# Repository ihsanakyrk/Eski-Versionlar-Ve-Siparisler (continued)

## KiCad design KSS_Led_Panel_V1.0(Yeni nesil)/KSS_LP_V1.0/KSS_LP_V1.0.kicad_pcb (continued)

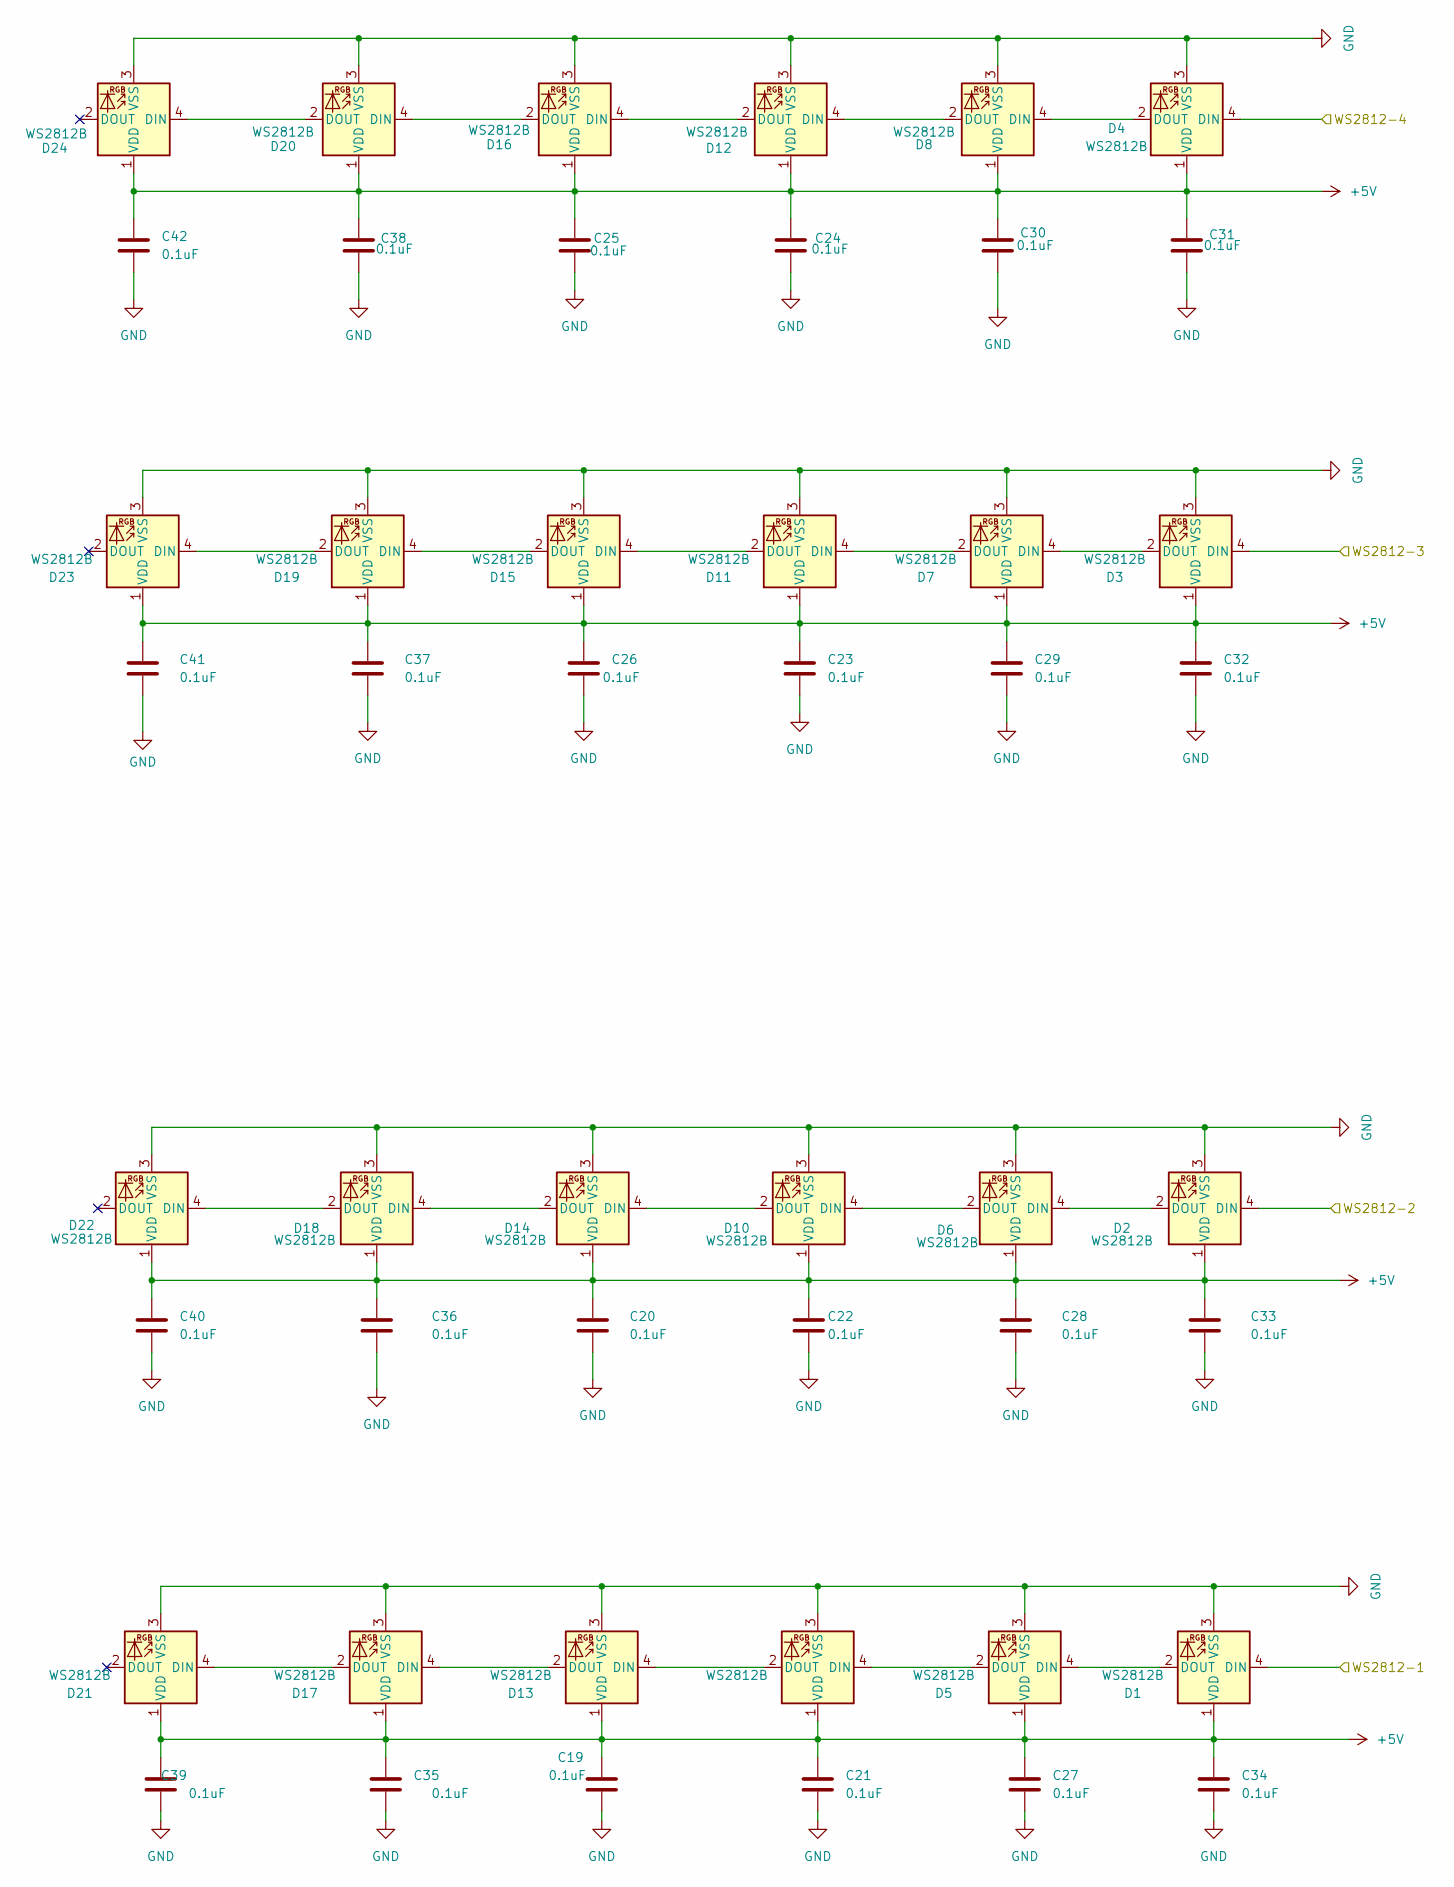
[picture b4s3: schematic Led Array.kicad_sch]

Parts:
C19, C20, C21, C22, C23, C24, C25, C26, C27, C28, C29, C30, C31, C32, C33, C34, C35, C36, C37, C38, C39, C40, C41, C42: 0.1uF; C_0603_1608Metric
D1, D2, D3, D4, D5, D6, D7, D8, D9, D10, D11, D12, D13, D14, D15, D16, D17, D18, D19, D20, D21, D22, D23, D24: WS2812B; LED_WS2812B_PLCC4_5.0x5.0mm_P3.2mm

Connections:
+5V: C19.1, C20.1, C21.1, C22.1, C23.1, C24.1, C25.1, C26.1, C27.1, C28.1, C29.1, C30.1, C31.1, C32.1, C33.1, C34.1, C35.1, C36.1, C37.1, C38.1, C39.1, C40.1, C41.1, C42.1, D1.1 (VDD), D2.1 (VDD), D3.1 (VDD), D4.1 (VDD), D5.1 (VDD), D6.1 (VDD), D7.1 (VDD), D8.1 (VDD), D9.1 (VDD), D10.1 (VDD), D11.1 (VDD), D12.1 (VDD), D13.1 (VDD), D14.1 (VDD), D15.1 (VDD), D16.1 (VDD), D17.1 (VDD), D18.1 (VDD), D19.1 (VDD), D20.1 (VDD), D21.1 (VDD), D22.1 (VDD), D23.1 (VDD), D24.1 (VDD); also elsewhere on the board
/Main_MCU/GPIO10: D4.4 (DIN); also elsewhere on the board
/Main_MCU/GPIO11: D3.4 (DIN); also elsewhere on the board
/Main_MCU/GPIO12: D2.4 (DIN); also elsewhere on the board
/Main_MCU/GPIO13: D1.4 (DIN); also elsewhere on the board
GND: C19.2, C20.2, C21.2, C22.2, C23.2, C24.2, C25.2, C26.2, C27.2, C28.2, C29.2, C30.2, C31.2, C32.2, C33.2, C34.2, C35.2, C36.2, C37.2, C38.2, C39.2, C40.2, C41.2, C42.2, D1.3 (VSS), D2.3 (VSS), D3.3 (VSS), D4.3 (VSS), D5.3 (VSS), D6.3 (VSS), D7.3 (VSS), D8.3 (VSS), D9.3 (VSS), D10.3 (VSS), D11.3 (VSS), D12.3 (VSS), D13.3 (VSS), D14.3 (VSS), D15.3 (VSS), D16.3 (VSS), D17.3 (VSS), D18.3 (VSS), D19.3 (VSS), D20.3 (VSS), D21.3 (VSS), D22.3 (VSS), D23.3 (VSS), D24.3 (VSS); also elsewhere on the board
unnamed: D1.2 (DOUT), D5.4 (DIN)
unnamed: D2.2 (DOUT), D6.4 (DIN)
unnamed: D3.2 (DOUT), D7.4 (DIN)
unnamed: D4.2 (DOUT), D8.4 (DIN)
unnamed: D5.2 (DOUT), D9.4 (DIN)
unnamed: D6.2 (DOUT), D10.4 (DIN)
unnamed: D10.2 (DOUT), D14.4 (DIN)
unnamed: D7.2 (DOUT), D11.4 (DIN)
unnamed: D11.2 (DOUT), D15.4 (DIN)
unnamed: D8.2 (DOUT), D12.4 (DIN)
unnamed: D12.2 (DOUT), D16.4 (DIN)
unnamed: D9.2 (DOUT), D13.4 (DIN)
unnamed: D13.2 (DOUT), D17.4 (DIN)
unnamed: D14.2 (DOUT), D18.4 (DIN)
unnamed: D15.2 (DOUT), D19.4 (DIN)
unnamed: D16.2 (DOUT), D20.4 (DIN)
unnamed: D17.2 (DOUT), D21.4 (DIN)
unnamed: D18.2 (DOUT), D22.4 (DIN)
unnamed: D19.2 (DOUT), D23.4 (DIN)
unnamed: D20.2 (DOUT), D24.4 (DIN)

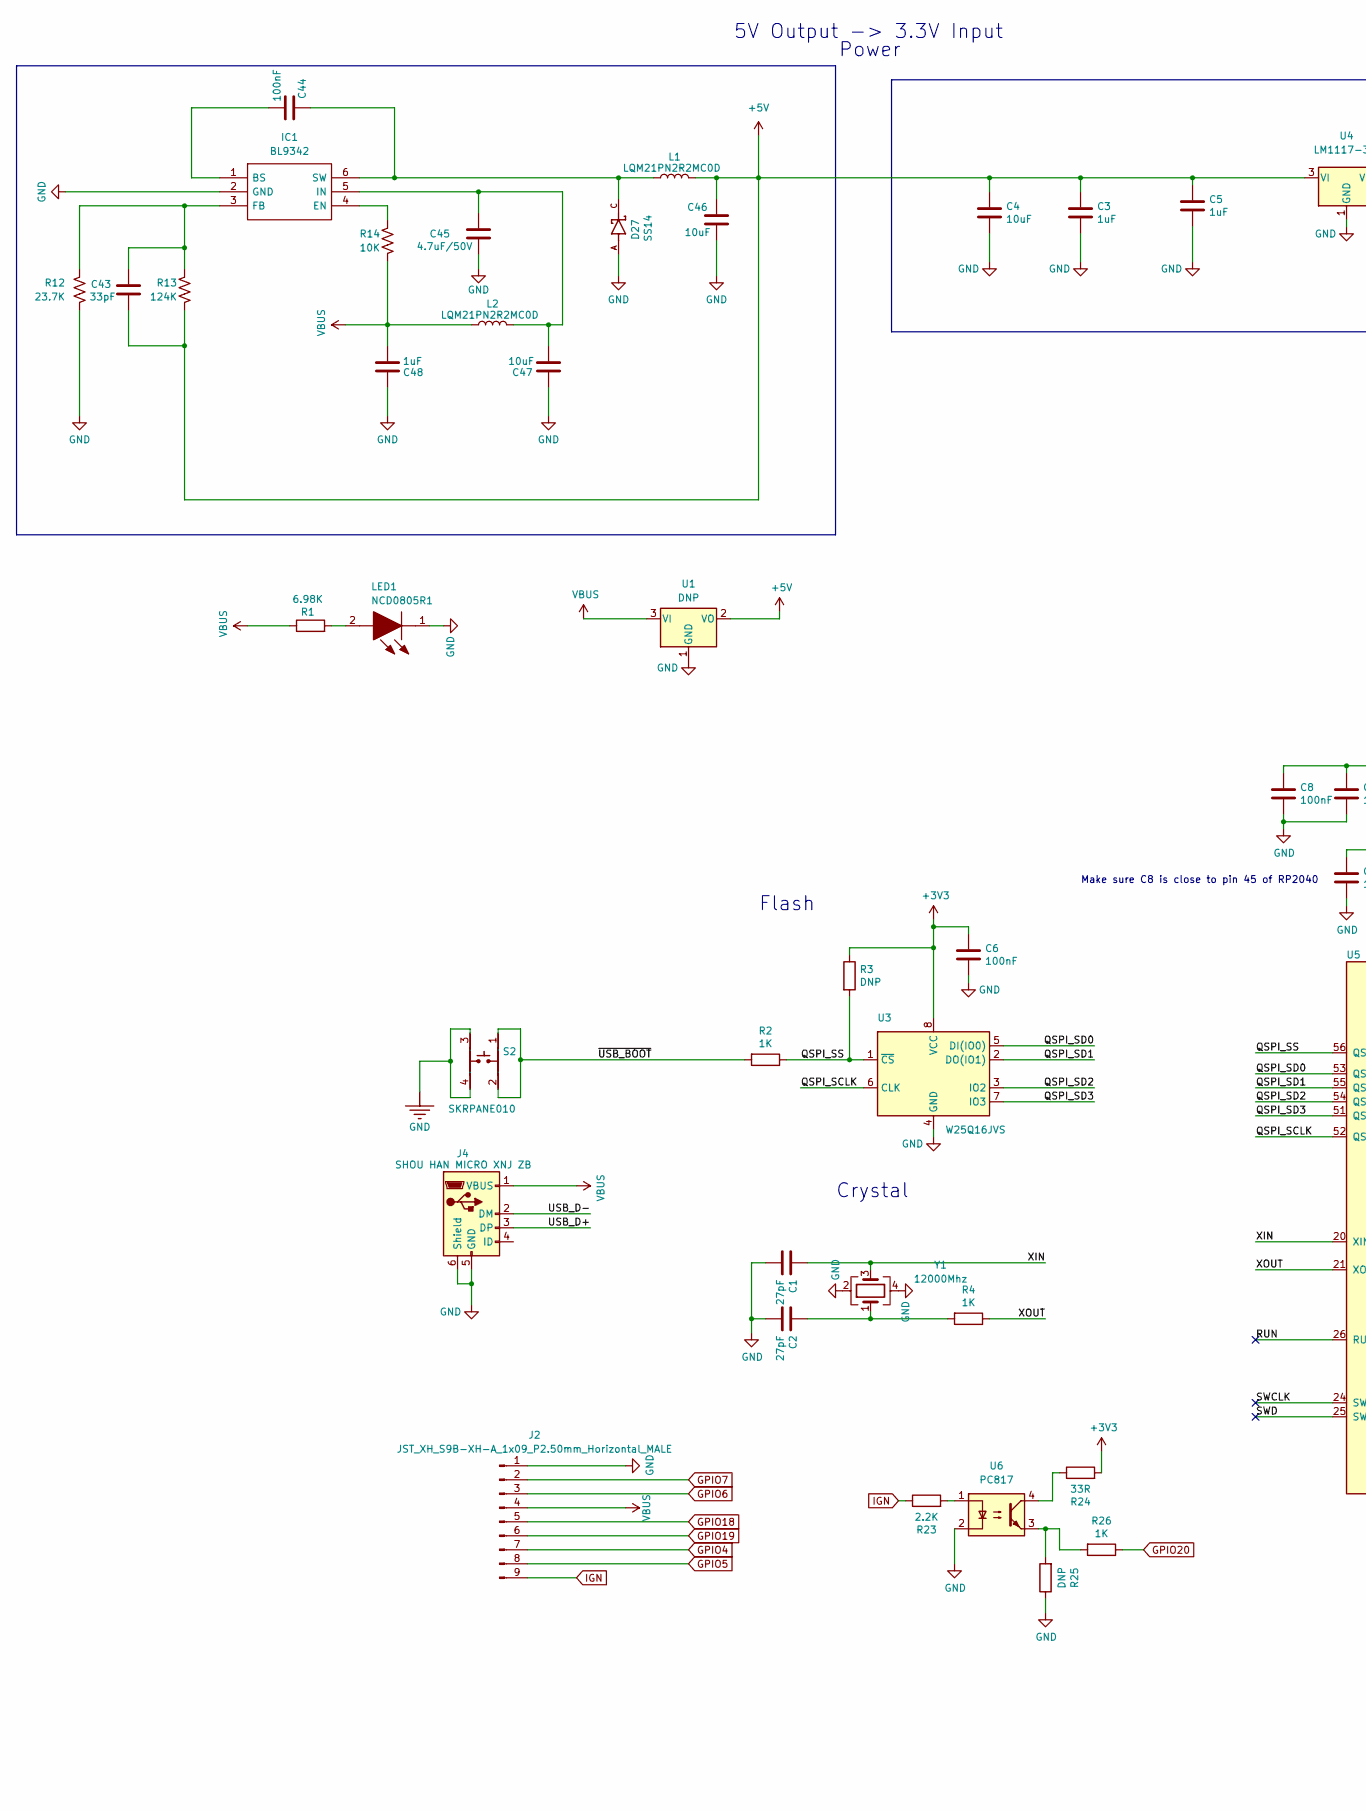
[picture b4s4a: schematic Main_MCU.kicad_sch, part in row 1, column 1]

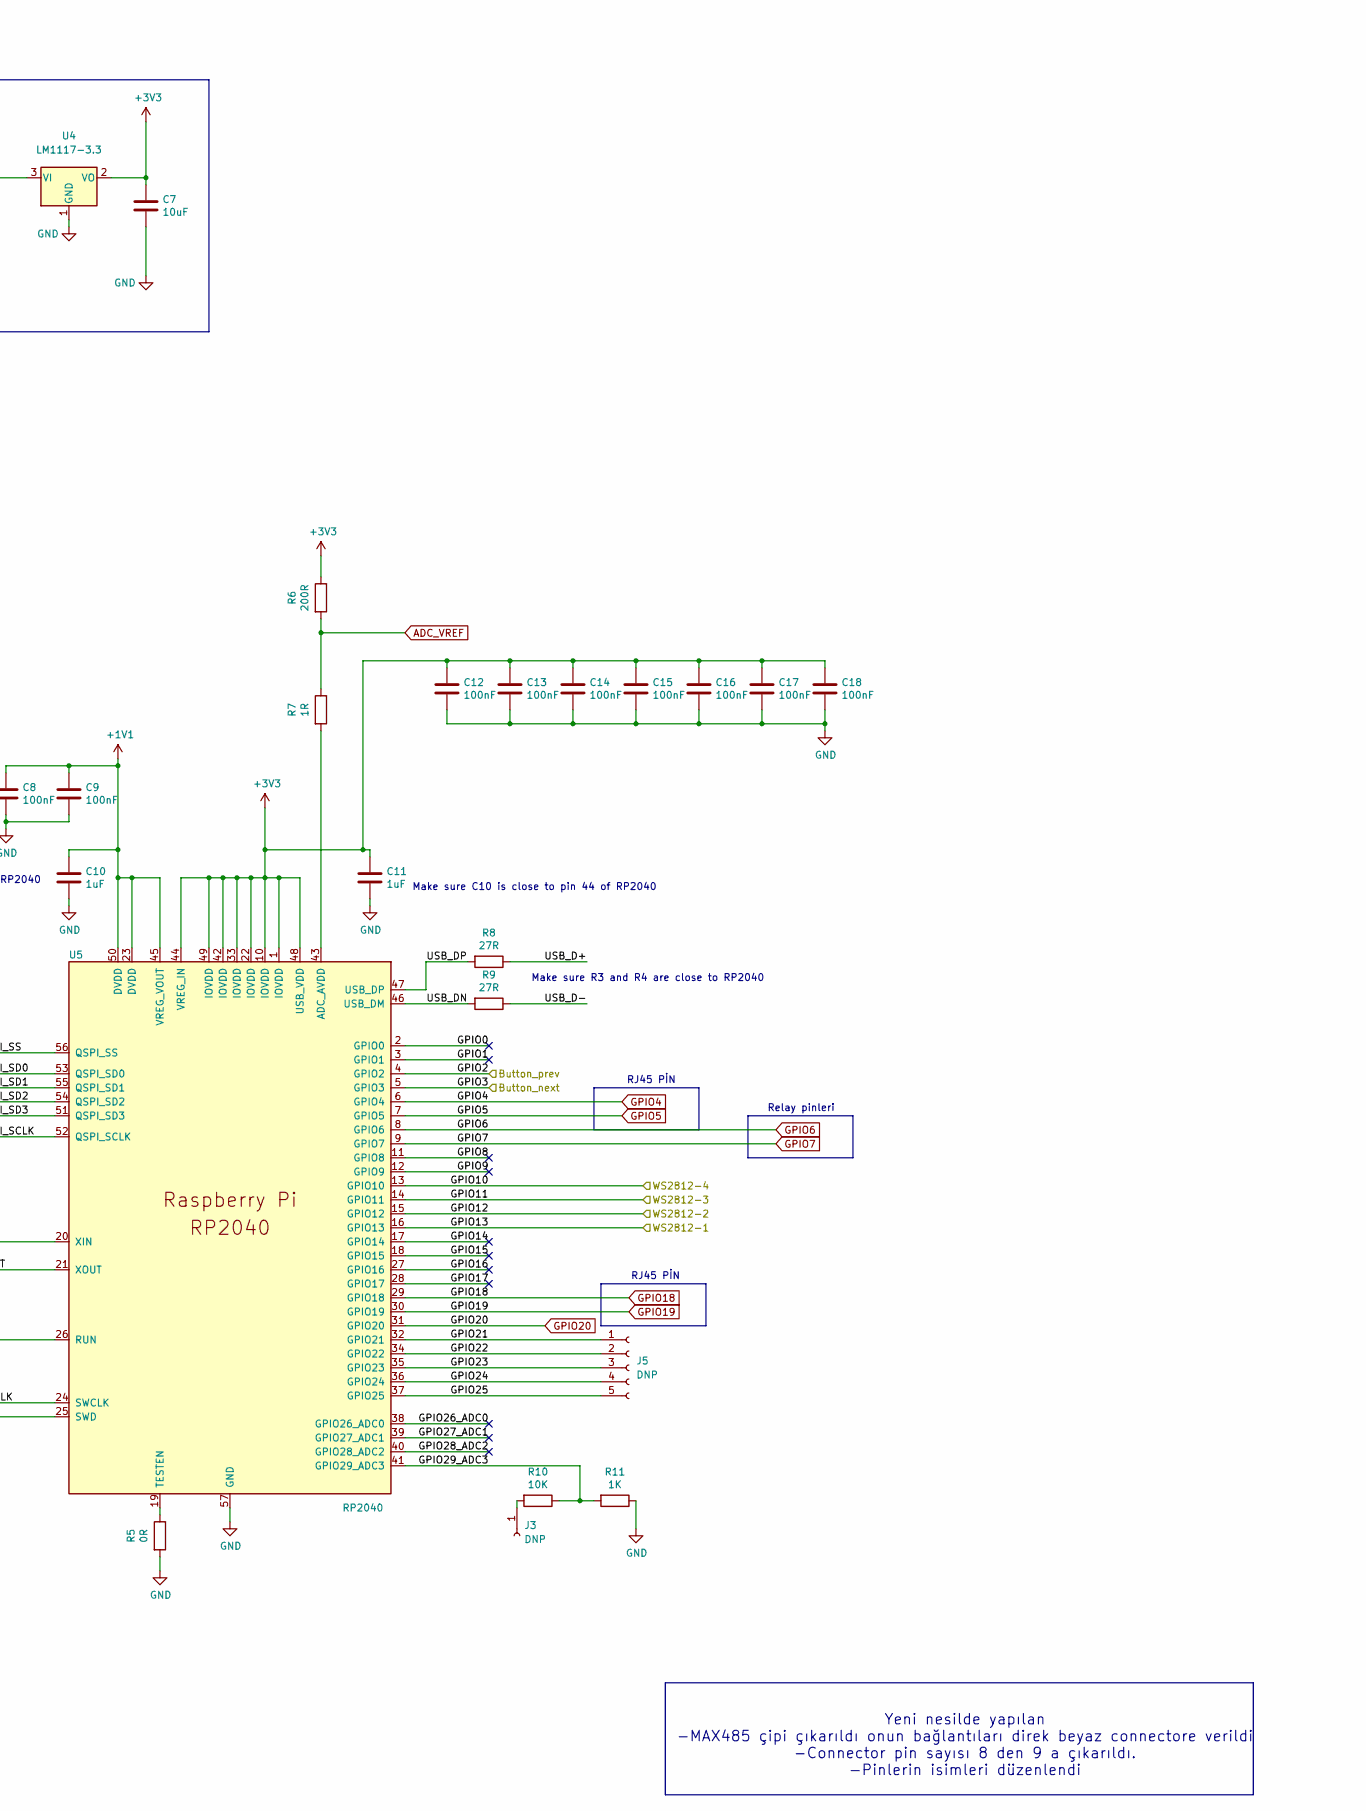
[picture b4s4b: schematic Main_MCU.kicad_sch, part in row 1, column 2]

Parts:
C1, C2: 27pF; C_0402_1005Metric
C3, C5: 1uF; C_0805_2012Metric
C4, C7: 10uF; C_0805_2012Metric
C6, C8, C9, C12, C13, C14, C15, C16, C17, C18: 100nF; C_0402_1005Metric
C10, C11: 1uF; C_0402_1005Metric
C43: 33pF; C_0603_1608Metric; MPN CL10C330JB8NNNC
C44: 100nF; C_0603_1608Metric; MPN 0603B104K500NT
C45: 4.7uF/50V; C_0603_1608Metric
C46, C47: 10uF; C_0603_1608Metric; MPN CL10A106MO8NQNC
C48: 1uF; C_0603_1608Metric
D27: SS14; MPN SS14 SOD-123FL
IC1: BL9342; SOT-23-6; MPN BL9342
J2: JST_XH_S9B-XH-A_1x09_P2.50mm_Horizontal_MALE; JST_XH_S9B-XH-A_1x09_P2.50mm_Horizontal
J3: DNP; PinHeader_1x01_P1.00mm_Vertical
J4: SHOU HAN MICRO XNJ ZB; Micro-B SMD; MPN SHOU HAN MICRO XNJ ZB
J5: DNP; PinHeader_1x05_P2.00mm_Vertical
L1, L2: LQM21PN2R2MC0D; L_0805_2012Metric; MPN LQM21PN2R2MC0D
LED1: NCD0805R1; LED_0805_2012Metric; Manufacturer_Part_Number 150080VS75000; Mouser Part Number 710-150080VS75000
R1: 6.98K; C_0402_1005Metric
R2, R4, R11, R26: 1K; C_0402_1005Metric
R3, R25: DNP; C_0402_1005Metric
R5: 0R; C_0402_1005Metric
R6: 200R; C_0402_1005Metric
R7: 1R; C_0402_1005Metric
R8, R9: 27R; C_0402_1005Metric
R10: 10K; C_0402_1005Metric
R12: 23.7K; R_0603_1608Metric
R13: 124K; R_0603_1608Metric
R14: 10K; R_0603_1608Metric; MPN 0603WAF1002T5E
R23: 2.2K; C_0402_1005Metric
R24: 33R; C_0402_1005Metric
S2: SKRPANE010
U1: DNP; SOT-223-3_TabPin2
U3: W25Q16JVS; SOIC-8_5.23x5.23mm_P1.27mm
U4: LM1117-3.3; SOT-223-3_TabPin2
U5: RP2040; RP2040-QFN-56
U6: PC817; DIP-4_W7.62mm_SMDSocket_SmallPads
Y1: 12000Mhz; Crystal_SMD_3225-4Pin_3.2x2.5mm

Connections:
+1V1: C8.1, C9.1, C10.1, U5.23 (DVDD), U5.45 (VREG_VOUT), U5.50 (DVDD)
+3V3: C6.1, C7.1, C11.1, C12.1, C13.1, C14.1, C15.1, C16.1, C17.1, C18.1, R3.1, R6.1, R24.2, U3.8 (VCC), U4.2 (VO), U5.1 (IOVDD), U5.10 (IOVDD), U5.22 (IOVDD), U5.33 (IOVDD), U5.42 (IOVDD), U5.44 (VREG_IN), U5.48 (USB_VDD), U5.49 (IOVDD)
+5V: C3.1, C4.1, C5.1, C43.1, C46.2, L1.1, R13.2, U1.2 (VO), U4.3 (VI); also elsewhere on the board
/Main_MCU/GPIO0: U5.2 (GPIO0)
/Main_MCU/GPIO1: U5.3 (GPIO1)
/Main_MCU/GPIO2: U5.4 (GPIO2); also elsewhere on the board
/Main_MCU/GPIO3: U5.5 (GPIO3); also elsewhere on the board
/Main_MCU/GPIO8: U5.11 (GPIO8)
/Main_MCU/GPIO9: U5.12 (GPIO9)
/Main_MCU/GPIO10: U5.13 (GPIO10); also elsewhere on the board
/Main_MCU/GPIO11: U5.14 (GPIO11); also elsewhere on the board
/Main_MCU/GPIO12: U5.15 (GPIO12); also elsewhere on the board
/Main_MCU/GPIO13: U5.16 (GPIO13); also elsewhere on the board
/Main_MCU/GPIO14: U5.17 (GPIO14)
/Main_MCU/GPIO15: U5.18 (GPIO15)
/Main_MCU/GPIO16: U5.27 (GPIO16)
/Main_MCU/GPIO17: U5.28 (GPIO17)
/Main_MCU/GPIO21: J5.1, U5.32 (GPIO21)
/Main_MCU/GPIO22: J5.2, U5.34 (GPIO22)
/Main_MCU/GPIO23: J5.3, U5.35 (GPIO23)
/Main_MCU/GPIO24: J5.4, U5.36 (GPIO24)
/Main_MCU/GPIO25: J5.5, U5.37 (GPIO25)
/Main_MCU/GPIO26_ADC0: U5.38 (GPIO26_ADC0)
/Main_MCU/GPIO27_ADC1: U5.39 (GPIO27_ADC1)
/Main_MCU/GPIO28_ADC2: U5.40 (GPIO28_ADC2)
/Main_MCU/GPIO29_ADC3: R10.1, R11.2, U5.41 (GPIO29_ADC3)
/Main_MCU/QSPI_SCLK: U3.6 (CLK), U5.52 (QSPI_SCLK)
/Main_MCU/QSPI_SD0: U3.5 (DI(IO0)), U5.53 (QSPI_SD0)
/Main_MCU/QSPI_SD1: U3.2 (DO(IO1)), U5.55 (QSPI_SD1)
/Main_MCU/QSPI_SD2: U3.3 (IO2), U5.54 (QSPI_SD2)
/Main_MCU/QSPI_SD3: U3.7 (IO3), U5.51 (QSPI_SD3)
/Main_MCU/QSPI_SS: R2.1, R3.2, U3.1 (~CS), U5.56 (QSPI_SS)
/Main_MCU/RUN: U5.26 (RUN)
/Main_MCU/SWCLK: U5.24 (SWCLK)
/Main_MCU/SWD: U5.25 (SWD)
/Main_MCU/USB_D+: J4.3 (DP), R8.1
/Main_MCU/USB_D-: J4.2 (DM), R9.1
/Main_MCU/USB_DN: R9.2, U5.46 (USB_DM)
/Main_MCU/USB_DP: R8.2, U5.47 (USB_DP)
/Main_MCU/XIN: C1.1, U5.20 (XIN), Y1.3
/Main_MCU/XOUT: R4.1, U5.21 (XOUT)
/Main_MCU/~USB_BOOT: R2.2, S2.1, S2.2
ADC_VREF: R6.2, R7.1
GND: C1.2, C2.2, C3.2, C4.2, C5.2, C6.2, C7.2, C8.2, C9.2, C10.2, C11.2, C12.2, C13.2, C14.2, C15.2, C16.2, C17.2, C18.2, C45.1, C46.1, C47.1, C48.1, D27.A, IC1.2 (GND), J2.1, J4.5 (GND), J4.6 (Shield), LED1.1, R5.2, R11.1, R12.2, R25.1, S2.3, S2.4, U1.1 (GND), U3.4 (GND), U4.1 (GND), U5.57 (GND), U6.2, Y1.2, Y1.4; also elsewhere on the board
GPIO4: J2.7, U5.6 (GPIO4)
GPIO5: J2.8, U5.7 (GPIO5)
GPIO6: J2.3, U5.8 (GPIO6)
GPIO7: J2.2, U5.9 (GPIO7)
GPIO18: J2.5, U5.29 (GPIO18)
GPIO19: J2.6, U5.30 (GPIO19)
GPIO20: R26.1, U5.31 (GPIO20)
IGN: J2.9, R23.1
unnamed: C2.1, R4.2, Y1.1
unnamed: C44.1, IC1.1 (BS)
unnamed: IC1.4 (EN), R14.1
unnamed: C43.2, IC1.3 (FB), R12.1, R13.1
unnamed: C45.2, C47.2, IC1.5 (IN), L2.1
unnamed: C44.2, D27.C, IC1.6 (SW), L1.2
unnamed: J3.1, R10.2
unnamed: LED1.2, R1.2
unnamed: R23.2, U6.1
unnamed: R24.1, U6.4
unnamed: R25.2, R26.2, U6.3
unnamed: R7.2, U5.43 (ADC_AVDD)
unnamed: R5.1, U5.19 (TESTEN)
VBUS: C48.2, J2.4, J4.1 (VBUS), L2.2, R1.1, R14.2, U1.3 (VI)

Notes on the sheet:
RJ45 PİN
Flash
Make sure C10 is close to pin 44 of RP2040
Relay pinleri
Power
Make sure C8 is close to pin 45 of RP2040
Crystal
5V Output -> 3.3V Input
Make sure R3 and R4 are close to RP2040
Yeni nesilde yapılan -MAX485 çipi çıkarıldı onun bağlantıları direk beyaz connectore verildi -Connector pin sayısı 8 den 9 a çıkarıldı. -Pinlerin isimleri düzenlendi

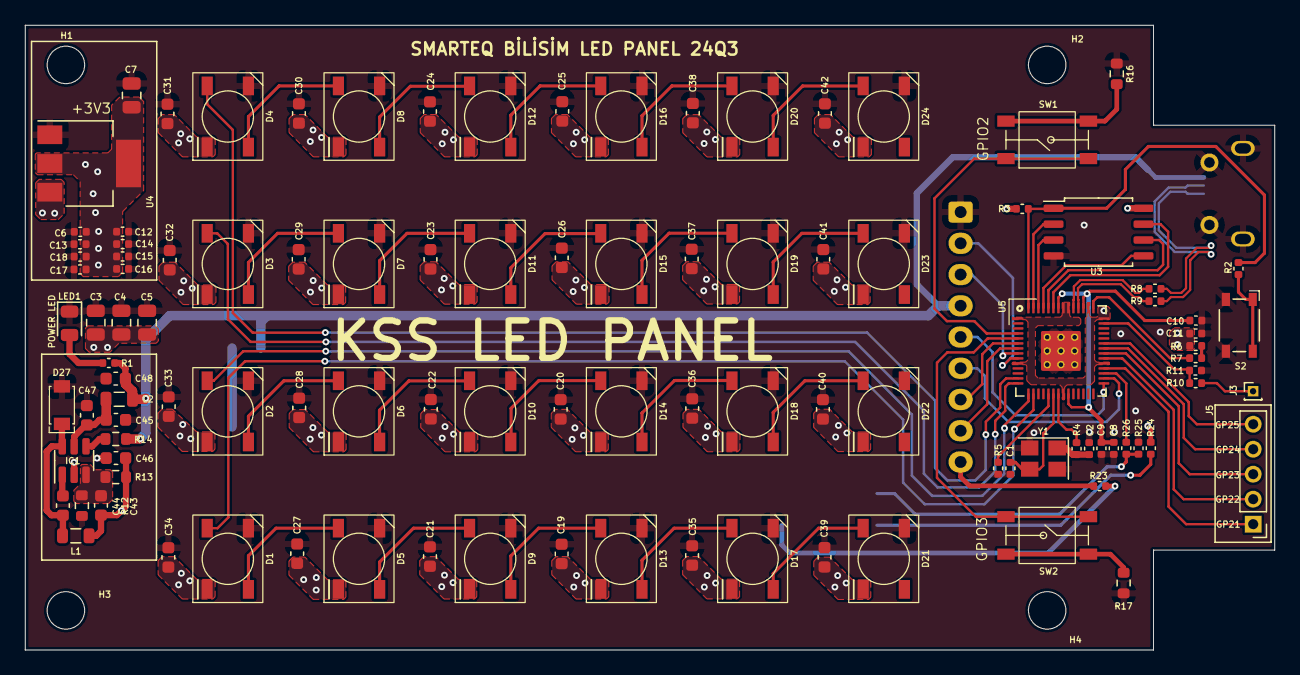
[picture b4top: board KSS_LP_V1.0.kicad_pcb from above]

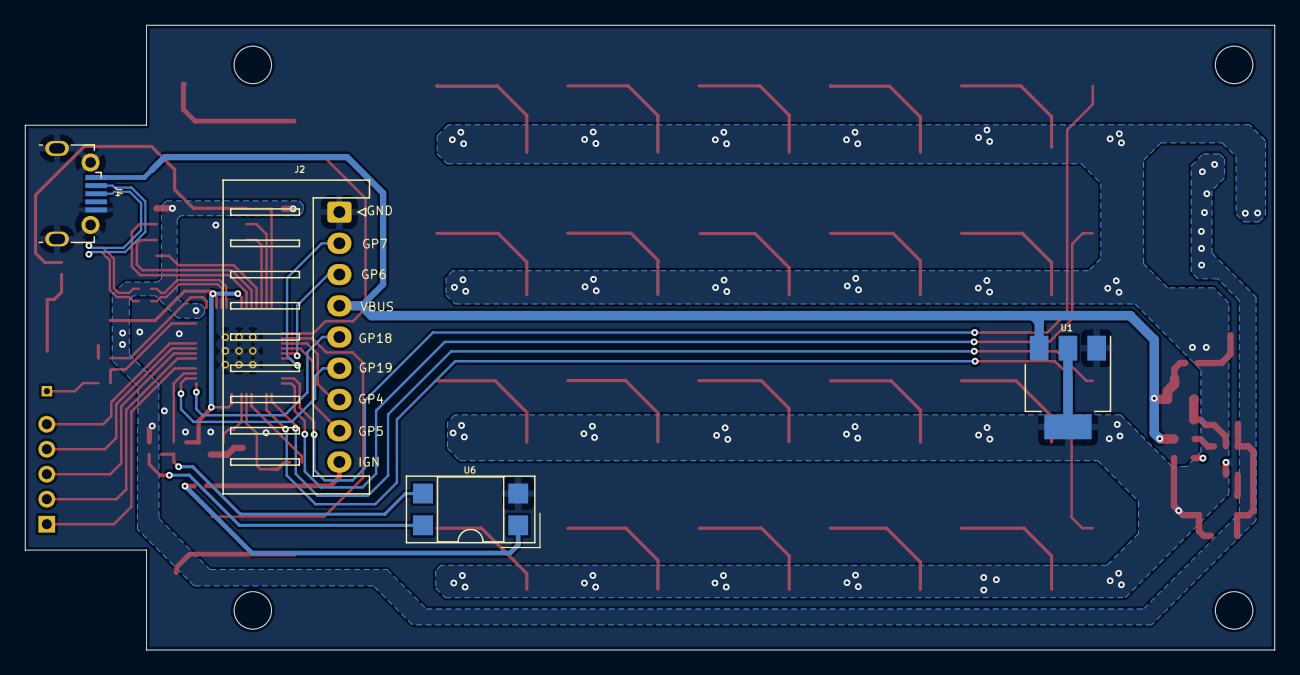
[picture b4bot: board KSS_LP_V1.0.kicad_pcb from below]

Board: 2 copper layers, 100.0 x 50.0 mm, 114 parts (4 on the bottom side), 74 nets.

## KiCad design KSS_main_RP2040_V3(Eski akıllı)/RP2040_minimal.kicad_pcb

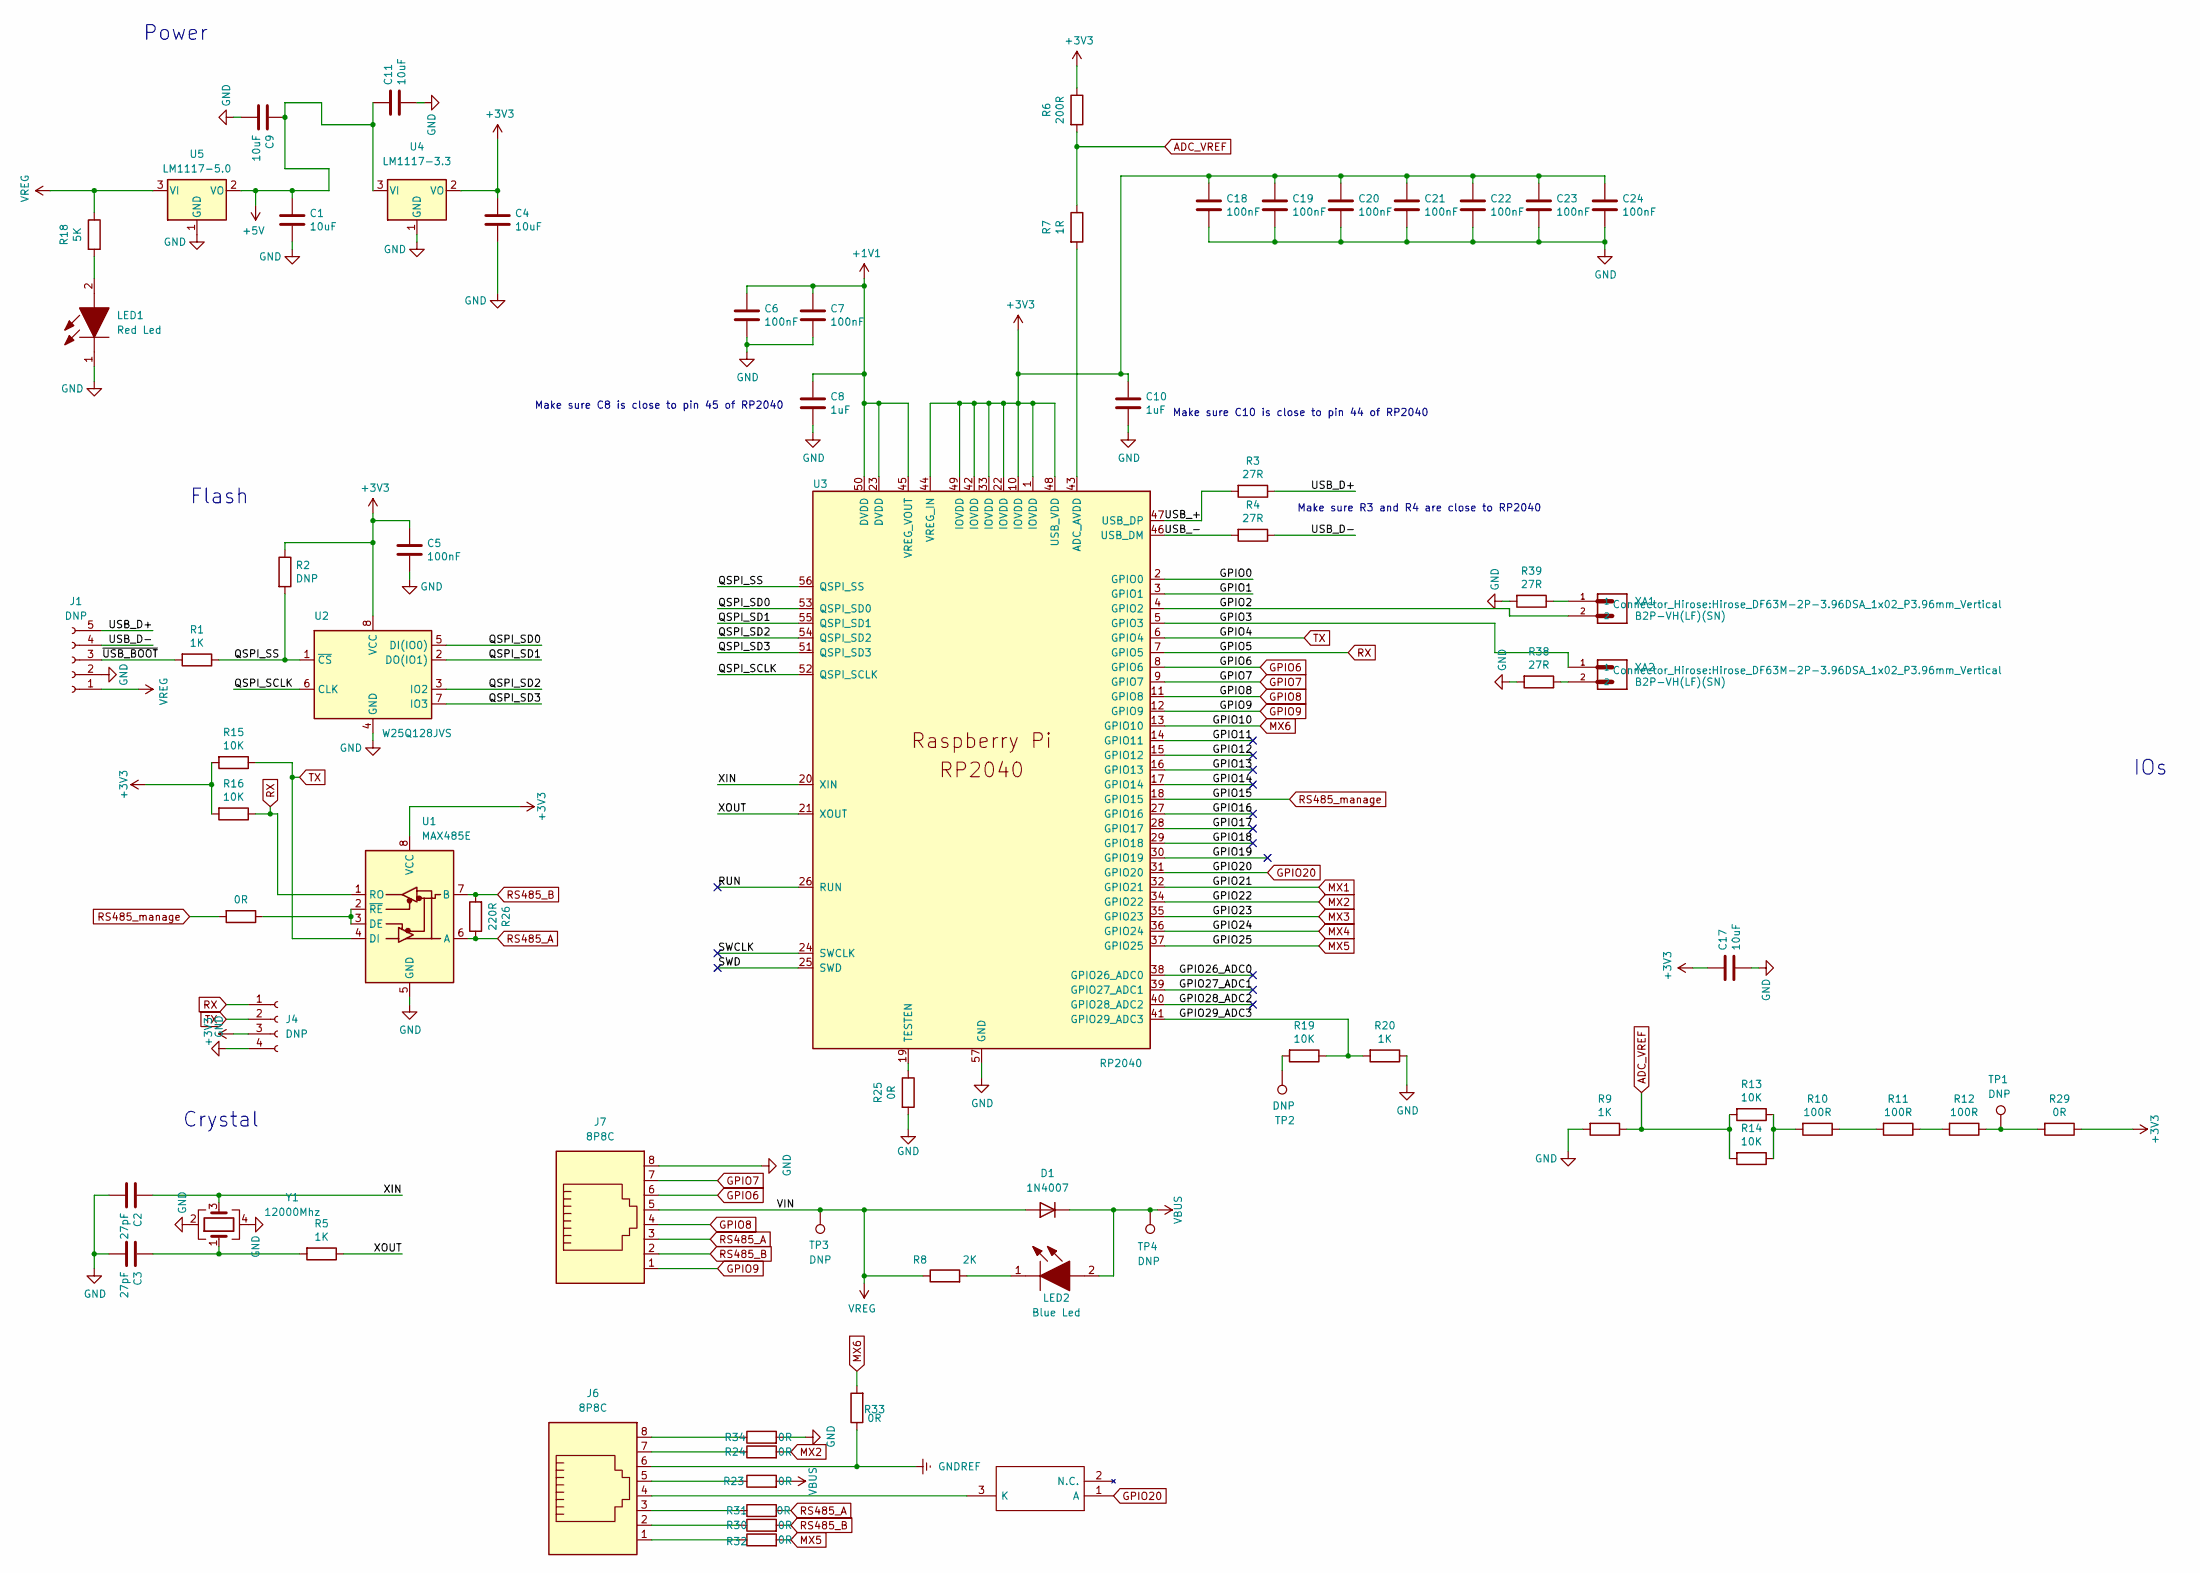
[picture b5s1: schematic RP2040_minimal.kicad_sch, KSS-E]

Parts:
C1, C4, C9, C11, C17: 10uF; C_0805_2012Metric
C2, C3: 27pF; C_0402_1005Metric
C5, C6, C7, C18, C19, C20, C21, C22, C23, C24: 100nF; C_0402_1005Metric
C8, C10: 1uF; C_0402_1005Metric
D1: 1N4007; D_SOD-123F; MPN 1N4007 (SOD-123FL)
D3: BAT854W; SOT65P210X110-3N; Manufacturer_Part_Number BAT854W; Mouser Part Number N/A
J1: DNP; PinHeader_1x05_P2.00mm_Vertical
J4: DNP; PinSocket_1x04_P2.00mm_Vertical
J6, J7: 8P8C; RJ45_Amphenol_54602-x08_Horizontal
LED1: Red Led; LED_0805_2012Metric
LED2: Blue Led; LED_0805_2012Metric
R1, R5, R9, R20: 1K; C_0402_1005Metric
R2: DNP; C_0402_1005Metric
R3, R4, R38, R39: 27R; C_0402_1005Metric
R6: 200R; C_0402_1005Metric
R7: 1R; C_0402_1005Metric
R8: 2K; C_0402_1005Metric
R10, R11, R12: 100R; C_0402_1005Metric
R13, R14, R15, R16, R19: 10K; C_0402_1005Metric
R18: 5K; C_0402_1005Metric
R23, R24, R25, R28, R29, R30, R31, R32, R33, R34: 0R; C_0402_1005Metric
R26: 220R; C_0402_1005Metric
TP1, TP2, TP3, TP4: DNP; TestPoint_Pad_1.0x1.0mm
U1: MAX485E; SOIC127P600X175-8N
U2: W25Q128JVS; SOIC-8_5.23x5.23mm_P1.27mm
U3: RP2040; RP2040-QFN-56
U4: LM1117-3.3; SOT-223-3_TabPin2
U5: LM1117-5.0; SOT-223-3_TabPin2
XA1, XA2: B2P-VH(LF)(SN); Hirose_DF63M-2P-3.96DSA_1x02_P3.96mm_Vertical
Y1: 12000Mhz; Crystal_SMD_3225-4Pin_3.2x2.5mm

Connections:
+1V1: C6.1, C7.1, C8.1, U3.23 (DVDD), U3.45 (VREG_VOUT), U3.50 (DVDD)
+3V3: C4.1, C5.1, C10.1, C17.1, C18.1, C19.1, C20.1, C21.1, C22.1, C23.1, C24.1, J4.3, R2.1, R6.1, R15.2, R16.2, R29.1, U1.8 (VCC), U2.8 (VCC), U3.1 (IOVDD), U3.10 (IOVDD), U3.22 (IOVDD), U3.33 (IOVDD), U3.42 (IOVDD), U3.44 (VREG_IN), U3.48 (USB_VDD), U3.49 (IOVDD), U4.2 (VO)
+5V: C1.1, C9.1, C11.1, U4.3 (VI), U5.2 (VO)
/GPIO0: U3.2 (GPIO0)
/GPIO1: U3.3 (GPIO1)
/GPIO2: U3.4 (GPIO2), XA1.2
/GPIO3: U3.5 (GPIO3), XA2.1
/GPIO11: U3.14 (GPIO11)
/GPIO12: U3.15 (GPIO12)
/GPIO13: U3.16 (GPIO13)
/GPIO14: U3.17 (GPIO14)
/GPIO16: U3.27 (GPIO16)
/GPIO17: U3.28 (GPIO17)
/GPIO18: U3.29 (GPIO18)
/GPIO19: U3.30 (GPIO19)
/GPIO26_ADC0: U3.38 (GPIO26_ADC0)
/GPIO27_ADC1: U3.39 (GPIO27_ADC1)
/GPIO28_ADC2: U3.40 (GPIO28_ADC2)
/GPIO29_ADC3: R19.1, R20.2, U3.41 (GPIO29_ADC3)
/QSPI_SCLK: U2.6 (CLK), U3.52 (QSPI_SCLK)
/QSPI_SD0: U2.5 (DI(IO0)), U3.53 (QSPI_SD0)
/QSPI_SD1: U2.2 (DO(IO1)), U3.55 (QSPI_SD1)
/QSPI_SD2: U2.3 (IO2), U3.54 (QSPI_SD2)
/QSPI_SD3: U2.7 (IO3), U3.51 (QSPI_SD3)
/QSPI_SS: R1.1, R2.2, U2.1 (~CS), U3.56 (QSPI_SS)
/RUN: U3.26 (RUN)
/SWCLK: U3.24 (SWCLK)
/SWD: U3.25 (SWD)
/USB_+: R3.2, U3.47 (USB_DP)
/USB_-: R4.2, U3.46 (USB_DM)
/USB_D+: J1.5, R3.1
/USB_D-: J1.4, R4.1
/XIN: C2.1, U3.20 (XIN), Y1.3
/XOUT: R5.1, U3.21 (XOUT)
/~USB_BOOT: J1.3, R1.2
ADC_VREF: R6.2, R7.1, R9.1, R13.2, R14.2
GND: C1.2, C2.2, C3.2, C4.2, C5.2, C6.2, C7.2, C8.2, C9.2, C10.2, C11.2, C17.2, C18.2, C19.2, C20.2, C21.2, C22.2, C23.2, C24.2, J1.2, J4.4, J7.8, LED1.1, R9.2, R20.1, R25.2, R34.2, R38.2, R39.2, U1.5 (GND), U2.4 (GND), U3.57 (GND), U4.1 (GND), U5.1 (GND), Y1.2, Y1.4
GNDREF: J6.6, R33.1
GPIO6: J7.6, U3.8 (GPIO6)
GPIO7: J7.7, U3.9 (GPIO7)
GPIO8: J7.4, U3.11 (GPIO8)
GPIO9: J7.1, U3.12 (GPIO9)
GPIO20: D3.1 (A), U3.31 (GPIO20)
MX1: U3.32 (GPIO21)
MX2: R24.2, U3.34 (GPIO22)
MX3: U3.35 (GPIO23)
MX4: U3.36 (GPIO24)
MX5: R32.2, U3.37 (GPIO25)
MX6: R33.2, U3.13 (GPIO10)
unnamed: C3.1, R5.2, Y1.1
unnamed: D3.3 (K), J6.4
unnamed: J6.1, R32.1
unnamed: J6.2, R30.1
unnamed: J6.3, R31.1
unnamed: J6.5, R23.1
unnamed: J6.7, R24.1
unnamed: J6.8, R34.1
unnamed: LED1.2, R18.2
unnamed: LED2.1, R8.2
unnamed: R10.1, R11.2
unnamed: R10.2, R13.1, R14.1
unnamed: R11.1, R12.2
unnamed: R12.1, R29.2, TP1.1
unnamed: R19.2, TP2.1
unnamed: R38.1, XA2.2
unnamed: R39.1, XA1.1
unnamed: R28.1, U1.2 (~RE), U1.3 (DE)
unnamed: R7.2, U3.43 (ADC_AVDD)
unnamed: R25.1, U3.19 (TESTEN)
RS485_A: J7.3, R26.1, R31.2, U1.6 (A)
RS485_B: J7.2, R26.2, R30.2, U1.7 (B)
RS485_manage: R28.2, U3.18 (GPIO15)
RX: J4.1, R16.1, U1.1 (RO), U3.7 (GPIO5)
TX: J4.2, R15.1, U1.4 (DI), U3.6 (GPIO4)
VBUS: D1.1 (K), LED2.2, R23.2, TP4.1
VREG: D1.2 (A), J1.1, J7.5, R8.1, R18.1, TP3.1, U5.3 (VI)

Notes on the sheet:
Make sure C8 is close to pin 45 of RP2040
Power
Flash
Make sure R3 and R4 are close to RP2040
Make sure C10 is close to pin 44 of RP2040
Crystal
IOs

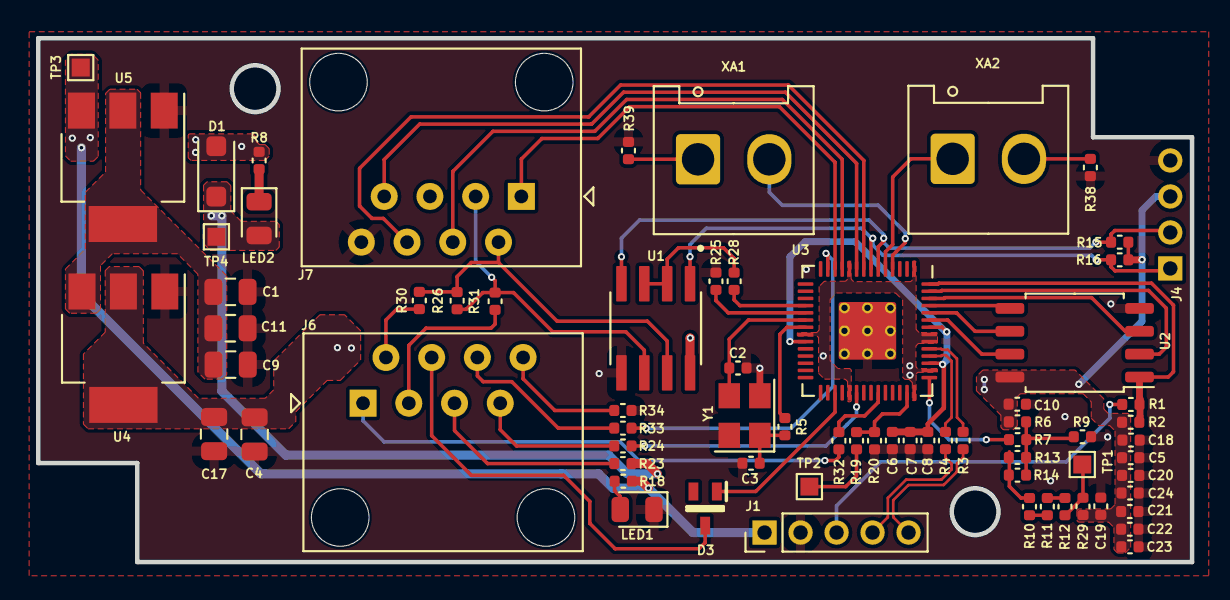
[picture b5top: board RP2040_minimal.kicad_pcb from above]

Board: 2 copper layers, 64.1 x 29.1 mm, 71 parts (0 on the bottom side), 57 nets.

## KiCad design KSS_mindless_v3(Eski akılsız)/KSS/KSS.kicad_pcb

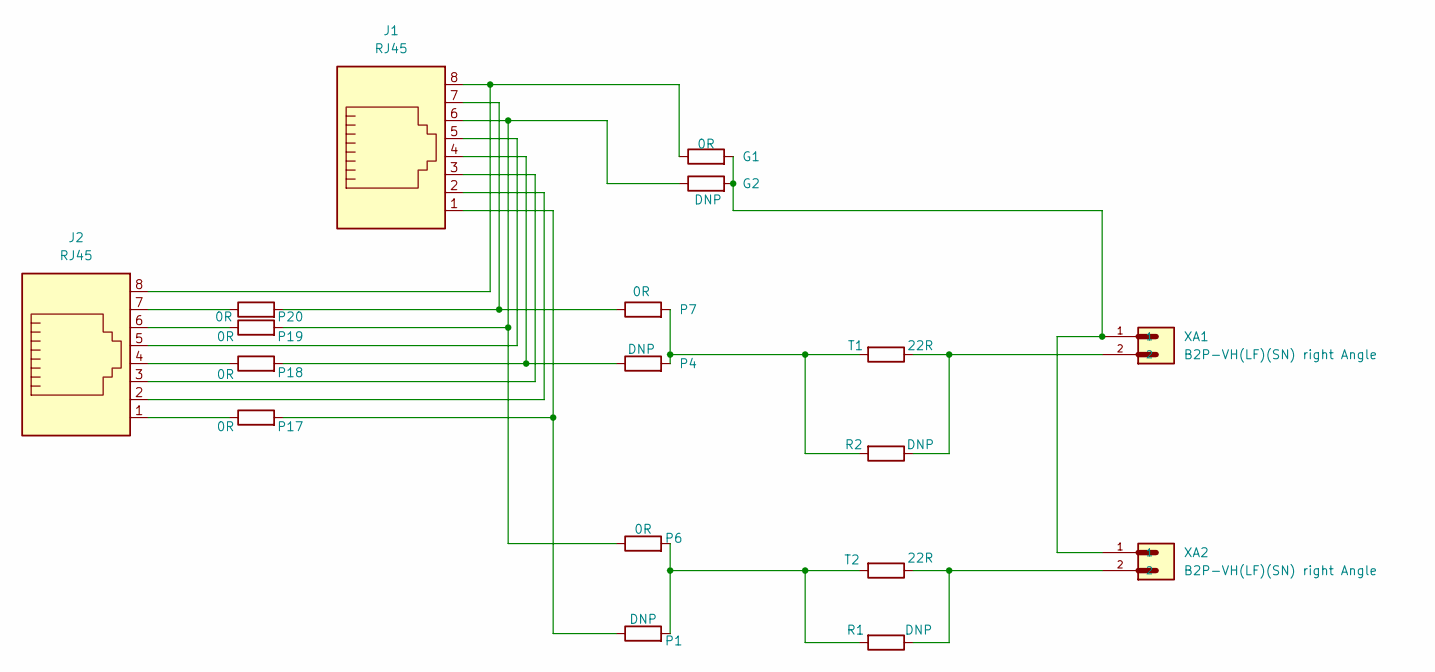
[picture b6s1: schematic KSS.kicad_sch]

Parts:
G1: 0R; R_0603_1608Metric
G2: DNP; R_0603_1608Metric
J1, J2: RJ45; RJ45_OST_PJ012-8P8CX_Vertical
P1, P4: DNP; R_0603_1608Metric
P6, P7: 0R; R_0603_1608Metric
P17, P18, P19, P20: 0R; R_0805_2012Metric
R1, R2: DNP; R_Box_L8.4mm_W2.5mm_P5.08mm
T1, T2: 22R; R_0603_1608Metric
XA1, XA2: B2P-VH(LF)(SN) right Angle; Hirose_DF63M-2P-3.96DSA_1x02_P3.96mm_Vertical

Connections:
unnamed: G1.1, J1.8, J2.8
unnamed: G1.2, G2.2, XA1.1, XA2.1
unnamed: G2.1, J1.6, P6.1, P19.2
unnamed: J1.1, P1.1, P17.2
unnamed: J1.2, J2.2
unnamed: J1.3, J2.3
unnamed: J1.4, P4.1, P18.2
unnamed: J1.5, J2.5
unnamed: J1.7, P7.1, P20.2
unnamed: J2.1, P17.1
unnamed: J2.4, P18.1
unnamed: J2.6, P19.1
unnamed: J2.7, P20.1
unnamed: P1.2, P6.2, R1.2, T2.2
unnamed: P4.2, P7.2, R2.2, T1.2
unnamed: R1.1, T2.1, XA2.2
unnamed: R2.1, T1.1, XA1.2

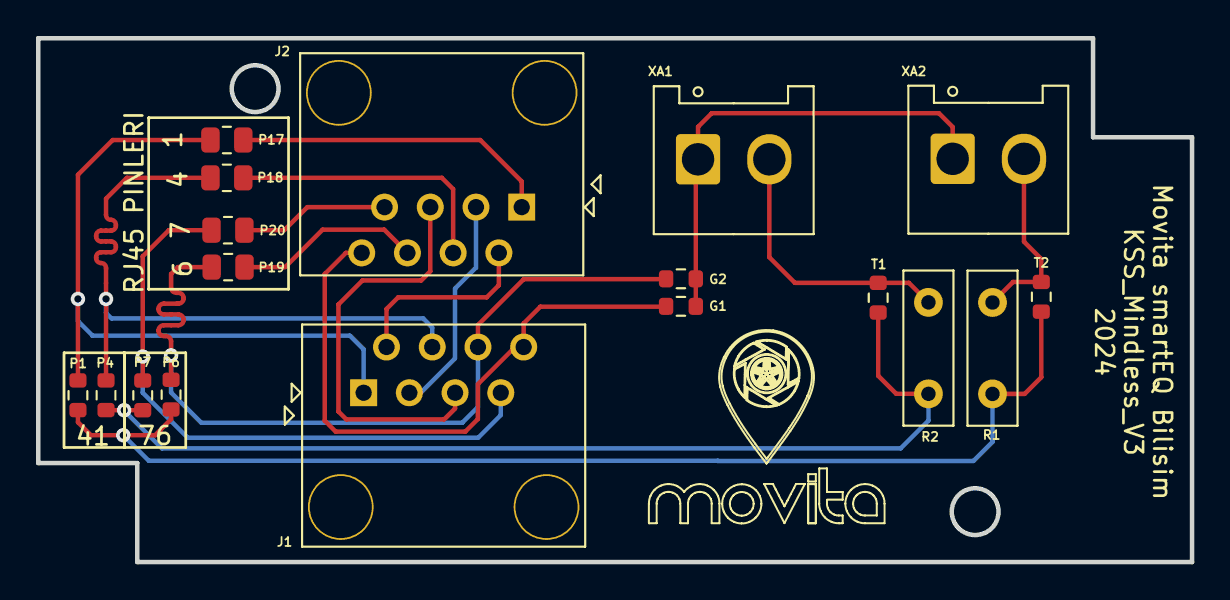
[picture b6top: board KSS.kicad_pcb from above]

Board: 2 copper layers, 64.1 x 29.1 mm, 18 parts (0 on the bottom side), 17 nets.
